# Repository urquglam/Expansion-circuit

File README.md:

# Expansion-circuit
This is an expansion board for aquariums, capable of connecting three outputs to various devices such as lights, pH sensors, temperature sensors, motors, etc.

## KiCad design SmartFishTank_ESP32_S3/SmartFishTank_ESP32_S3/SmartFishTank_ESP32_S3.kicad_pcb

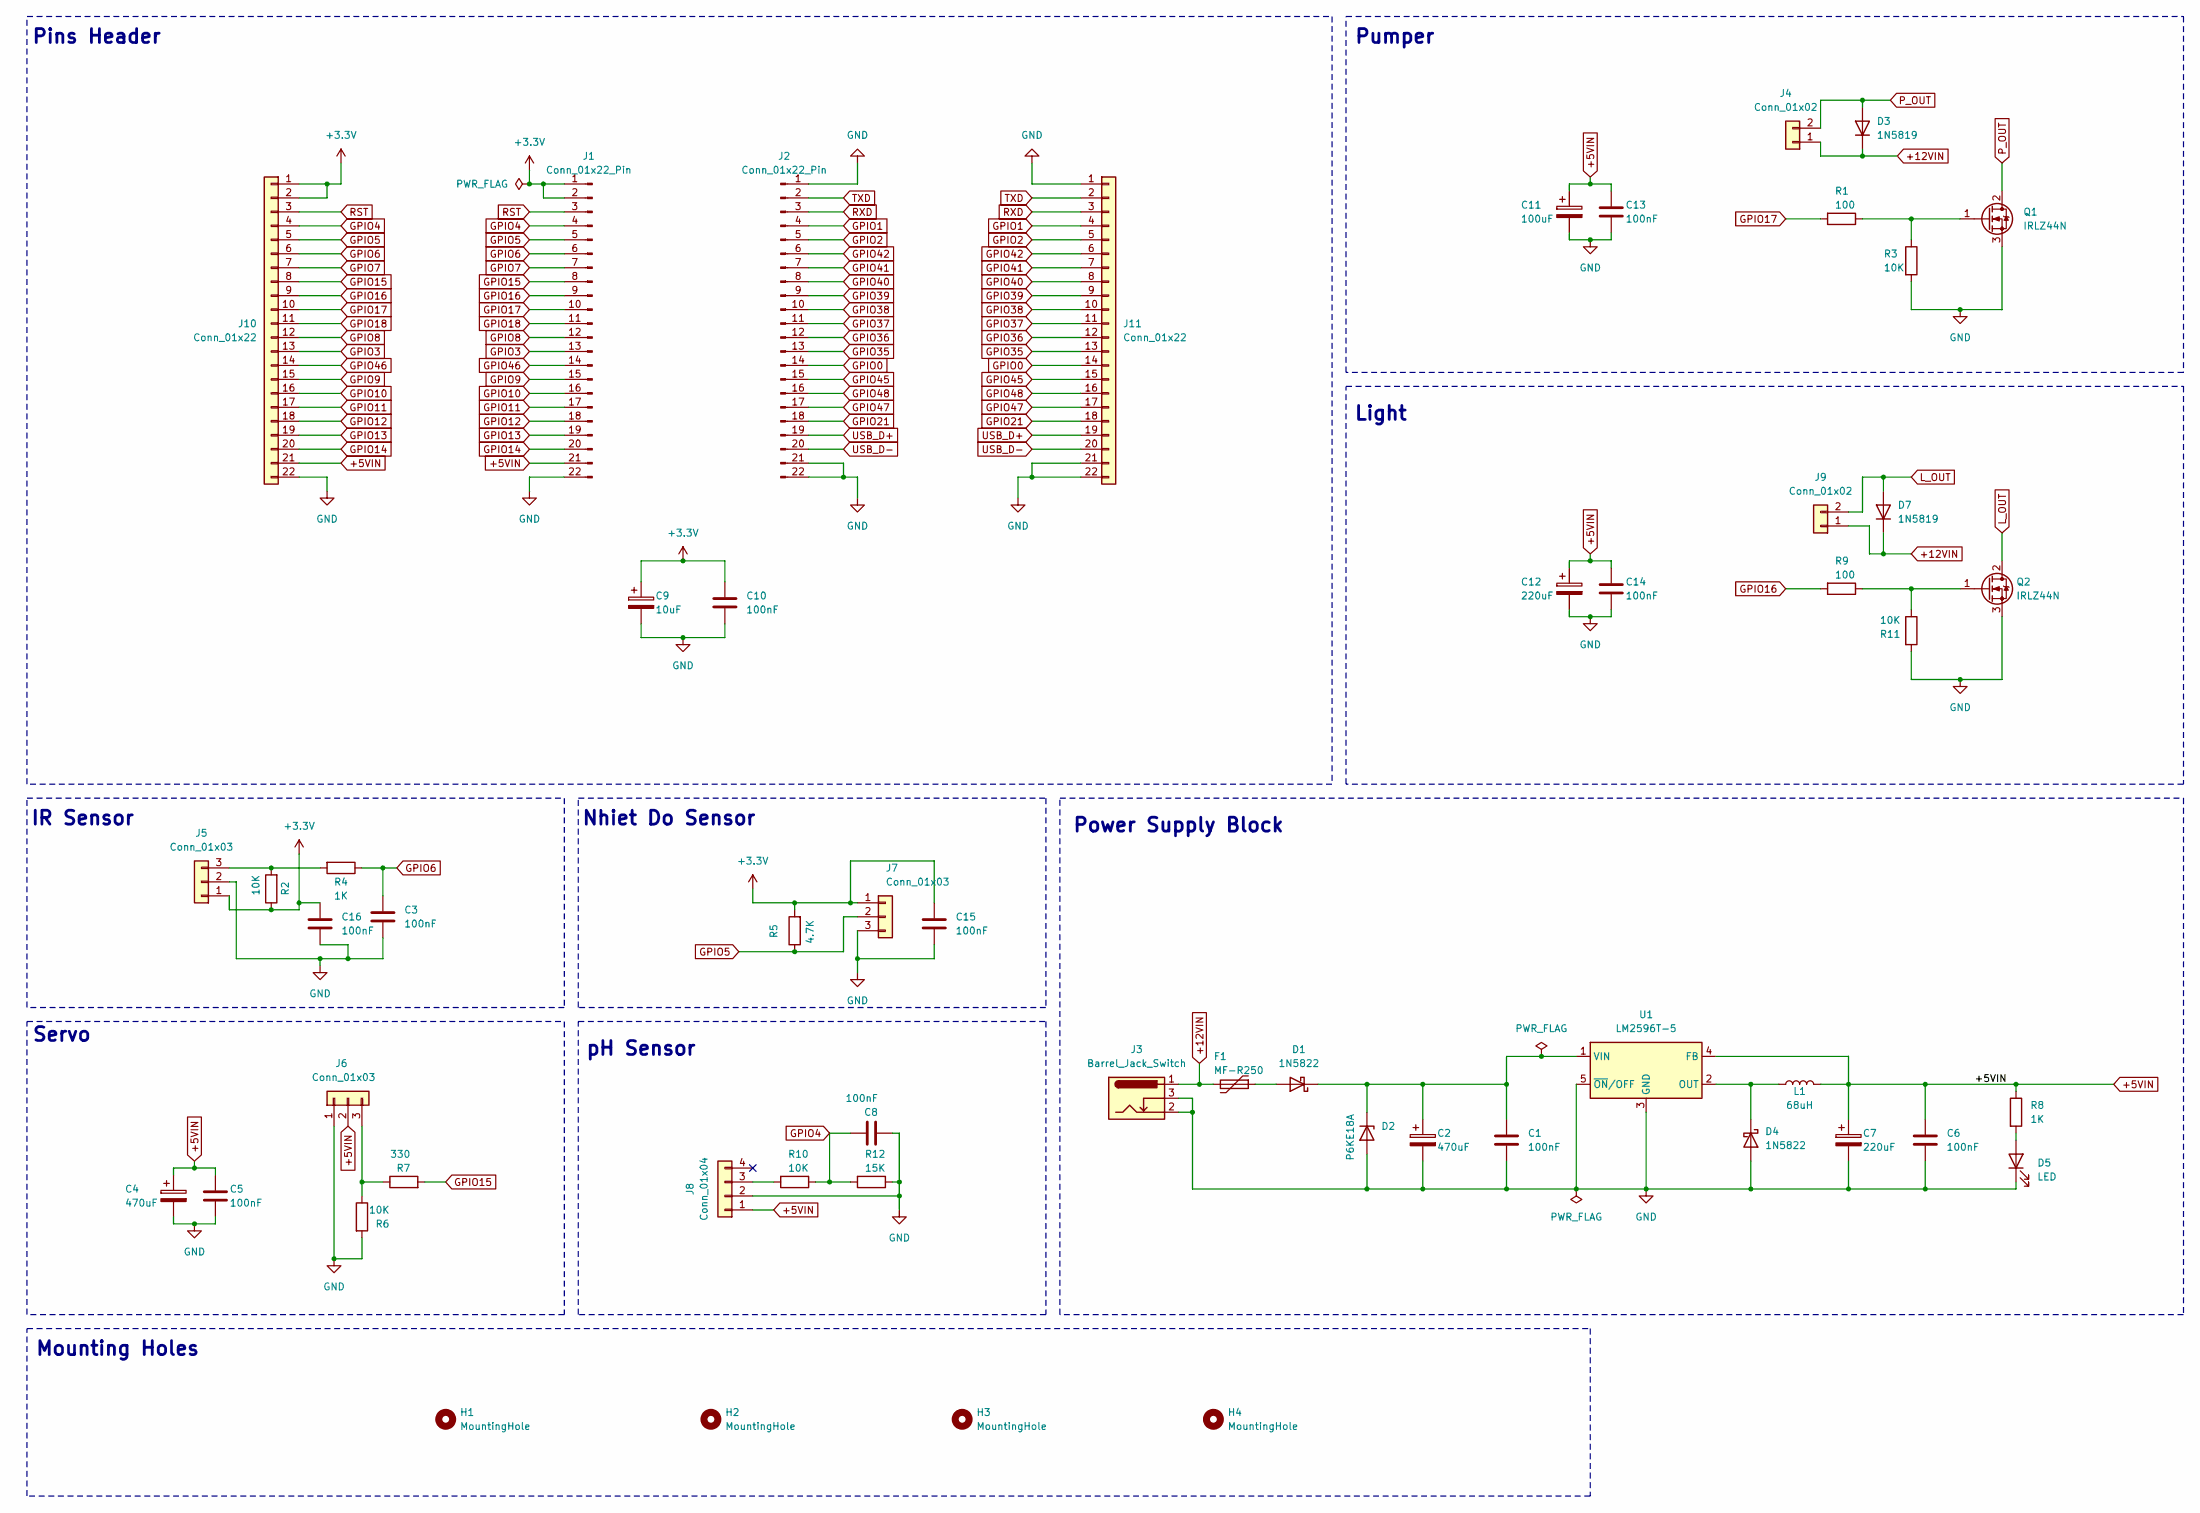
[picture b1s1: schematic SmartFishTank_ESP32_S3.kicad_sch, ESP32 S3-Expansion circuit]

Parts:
C1, C3, C5, C6, C8, C10, C13, C14, C15, C16: 100nF; C_Disc_D5.0mm_W2.5mm_P5.00mm
C2, C4: 470uF; CP_Radial_D10.0mm_P5.00mm
C7: 220uF; CP_Radial_D6.3mm_P2.50mm
C9: 10uF; CP_Radial_D10.0mm_P5.00mm
C11: 100uF; CP_Radial_D10.0mm_P5.00mm
C12: 220uF; CP_Radial_D10.0mm_P5.00mm
D1, D4: 1N5822; D_DO-201AD_P15.24mm_Horizontal
D2: P6KE18A; D_DO-15_P10.16mm_Horizontal
D3, D7: 1N5819; D_DO-41_SOD81_P10.16mm_Horizontal
D5: LED
F1: MF-R250; Fuse_Bourns_MF-RG400
H1, H2, H3, H4: MountingHole; MountingHole_3.2mm_M3
J1, J2: Conn_01x22_Pin; PinSocket_1x22_P2.54mm_Vertical
J3: Barrel_Jack_Switch; BarrelJack_Horizontal
J4, J9: Conn_01x02; TerminalBlock_Phoenix_MKDS-1,5-2-5.08_1x02_P5.08mm_Horizont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
J5, J6: Conn_01x03; PinHeader_1x03_P2.54mm_Vertical
J7: Conn_01x03; TerminalBlock_Phoenix_MKDS-1,5-3-5.08_1x03_P5.08mm_Horizont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
J8: Conn_01x04; PinHeader_1x04_P2.54mm_Vertical
J10, J11: Conn_01x22; PinHeader_1x22_P2.54mm_Vertical
L1: 68uH; L_Radial_D10.0mm_P5.00mm_Fastron_07M
Q1, Q2: IRLZ44N; TO-220-3_Vertical
R1, R9: 100; R_Axial_DIN0207_L6.3mm_D2.5mm_P10.16mm_Horizontal
R2, R3, R6, R10, R11: 10K; R_Axial_DIN0207_L6.3mm_D2.5mm_P10.16mm_Horizontal
R4, R8: 1K; R_Axial_DIN0207_L6.3mm_D2.5mm_P10.16mm_Horizontal
R5: 4.7K; R_Axial_DIN0207_L6.3mm_D2.5mm_P10.16mm_Horizontal
R7: 330; R_Axial_DIN0207_L6.3mm_D2.5mm_P10.16mm_Horizontal
R12: 15K; R_Axial_DIN0207_L6.3mm_D2.5mm_P10.16mm_Horizontal
U1: LM2596T-5; TO-220-5_P3.4x3.7mm_StaggerOdd_Lead3.8mm_Vertical

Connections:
+3.3V: C9.1, C10.1, C15.1, C16.1, J1.1, J1.2, J5.1, J7.1, J10.1, J10.2, R2.1, R5.2
+5VIN: C4.1, C5.2, C6.1, C7.1, C11.1, C12.1, C13.2, C14.2, J1.21, J6.2, J8.1, J10.21, L1.2, R8.1, U1.4 (FB)
+12VIN: D3.1 (K), D7.1 (K), F1.2, J3.1, J4.1, J9.1
GND: C1.2, C2.2, C3.2, C4.2, C5.1, C6.2, C7.2, C8.2, C9.2, C10.2, C11.2, C12.2, C13.1, C14.1, C15.2, C16.2, D2.2 (A), D4.2 (A), D5.1 (K), J1.22, J2.1, J2.21, J2.22, J3.2, J3.3, J5.2, J6.1, J7.3, J8.2, J10.22, J11.1, J11.21, J11.22, Q1.3 (S), Q2.3 (S), R3.2, R6.2, R11.2, R12.1, U1.3 (GND), U1.5 (~ON/OFF)
GPIO0: J2.14, J11.14
GPIO1: J2.4, J11.4
GPIO2: J2.5, J11.5
GPIO3: J1.13, J10.13
GPIO4: C8.1, J1.4, J10.4, R10.1, R12.2
GPIO5: J1.5, J7.2, J10.5, R5.1
GPIO6: C3.1, J1.6, J10.6, R4.1
GPIO7: J1.7, J10.7
GPIO8: J1.12, J10.12
GPIO9: J1.15, J10.15
GPIO10: J1.16, J10.16
GPIO11: J1.17, J10.17
GPIO12: J1.18, J10.18
GPIO13: J1.19, J10.19
GPIO14: J1.20, J10.20
GPIO15: J1.8, J10.8, R7.2
GPIO16: J1.9, J10.9, R9.2
GPIO17: J1.10, J10.10, R1.2
GPIO18: J1.11, J10.11
GPIO21: J2.18, J11.18
GPIO35: J2.13, J11.13
GPIO36: J2.12, J11.12
GPIO37: J2.11, J11.11
GPIO38: J2.10, J11.10
GPIO39: J2.9, J11.9
GPIO40: J2.8, J11.8
GPIO41: J2.7, J11.7
GPIO42: J2.6, J11.6
GPIO45: J2.15, J11.15
GPIO46: J1.14, J10.14
GPIO47: J2.17, J11.17
GPIO48: J2.16, J11.16
L_OUT: D7.2 (A), J9.2, Q2.2 (D)
unnamed: D1.2 (A), F1.1
unnamed: C1.1, C2.1, D1.1 (K), D2.1 (K), U1.1 (VIN)
unnamed: D4.1 (K), L1.1, U1.2 (OUT)
unnamed: D5.2 (A), R8.2
unnamed: J5.3, R2.2, R4.2
unnamed: J6.3, R6.1, R7.1
unnamed: J8.3, R10.2
unnamed: Q1.1 (G), R1.1, R3.1
unnamed: Q2.1 (G), R9.1, R11.1
P_OUT: D3.2 (A), J4.2, Q1.2 (D)
RST: J1.3, J10.3
RXD: J2.3, J11.3
TXD: J2.2, J11.2
USB_D+: J2.19, J11.19
USB_D-: J2.20, J11.20

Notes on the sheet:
Mounting Holes
Pins Header
Pumper
Light
Nhiet Do Sensor
Servo
IR Sensor
pH Sensor
Power Supply Block

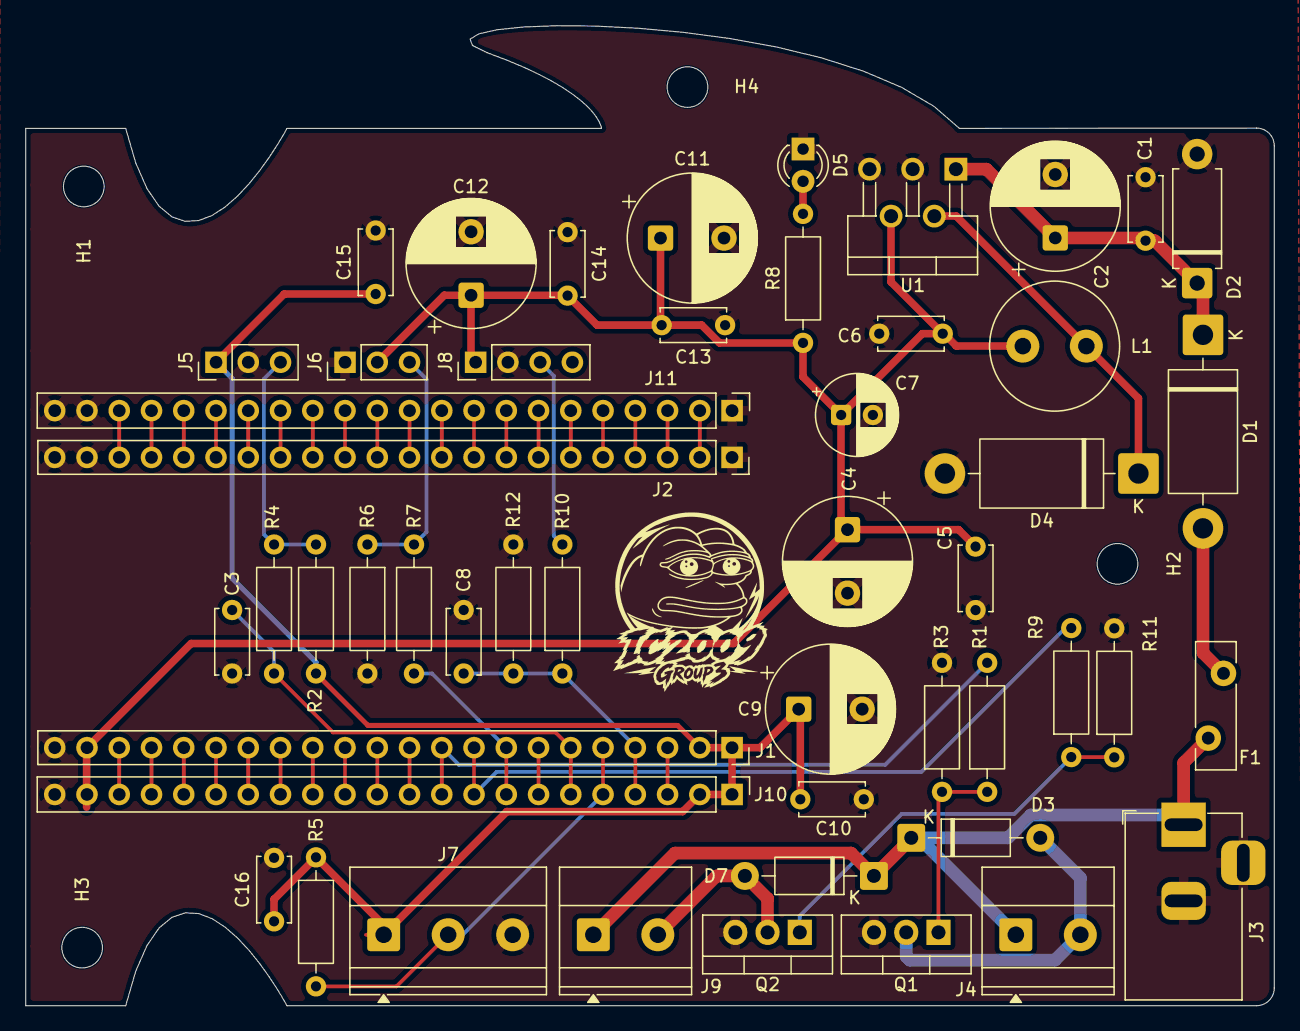
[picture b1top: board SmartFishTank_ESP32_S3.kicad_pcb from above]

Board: 2 copper layers, 98.3 x 77.2 mm, 54 parts (0 on the bottom side), 52 nets.
